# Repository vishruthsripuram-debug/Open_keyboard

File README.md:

# Nano pad
A 4 key macro pad that you can program actions to.

## Design
My inspiration for this macro pad was the printed pad by prota design but i wanted to make something smaller and cheaper than both of their offering the printed pad and glyff. The printed pad being $68 seemed quite unreasonable to me seeing as it was only a screen a few key swicthes and a microcontroller.

I wanted the project to be simple and easily accessible and customisable by many people so all of the PCB design files are included in the rep for download and printing from a pcb service. The case is 3d printable in any colour you like and customisable to include a knob or other features as step and other cad files are included. The model has also been published on makerworld for the ease of use with Bambulab printers. The whole idea is to hace a simple good looking macro pad that anyone can own for under $15 USD, for 25 USD you can own 5 macro pads.

## BOM

## Bill of Materials — Macro Pad

| Item # | Designator | Qty | Manufacturer | Mfg Part # | Description / Value | Package/Footprint | Type | Notes |
|---|---|---|---|---|---|---|---|---|
| 1 | SW1, SW2, SW3, SW4 | 4 | Cherry (preferred) | MX1A-G1NW | MX Brown, tactile, PCB mount, 5-pin | SW_Cherry_MX_1.00u_PCB | THT | If out of stock, substitute OK: any 5-pin PCB-mount MX-compatible Brown tactile switch (e.g. Gateron KS-3 Brown, Kailh Box/MX Brown, Outemu Brown) — all fit this footprint |
| 2 | U1 | 1 | DFRobot | DFR0648 | Fermion 0.91" 128x32 SSD1306 OLED, I2C, top-mounted pin header (OLED-B) | Module, pin header, THT | THT | Pins are on the short top edge, NOT the long side — confirm this exact pinout before substituting |
| 3 | U2 | 1 | Seeed Studio | 101991470 | XIAO ESP32-C6 module (Tape and Reel, SMD variant) | SMD castellated module | SMD | — |

## Software

## Collaboration
In collaboration with PCBWay

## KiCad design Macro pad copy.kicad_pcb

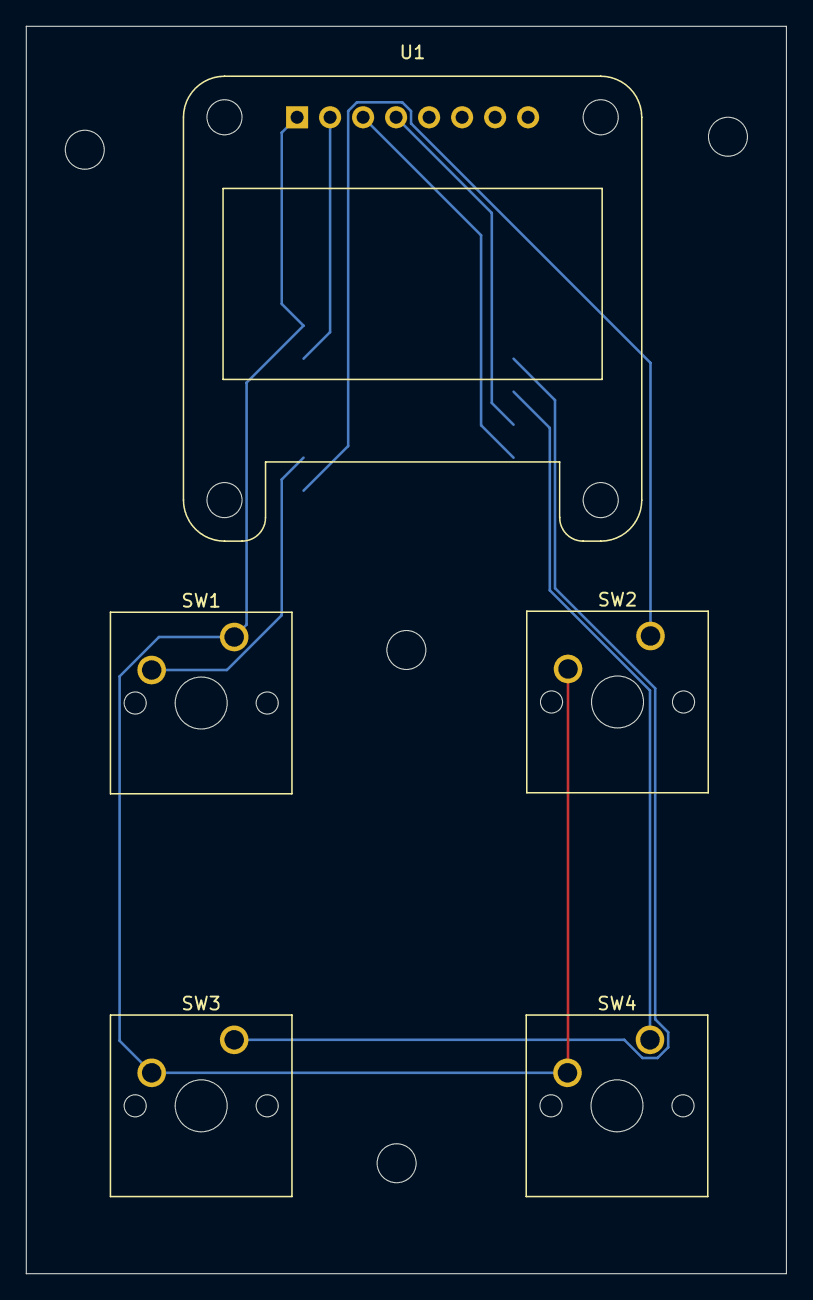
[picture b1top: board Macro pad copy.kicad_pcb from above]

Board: 2 copper layers, 58.5 x 96.0 mm, 6 parts (1 on the bottom side), 8 nets.

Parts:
SW1, SW2, SW3, SW4: SW_Push; SW_Cherry_MX_1.00u_PCB
U1: ER_OLEDM0.91_1x-I2C; Adafruit_SSD1306
U2: MOUDLE-SEEEDUINO-XIAO; XIAO-ESP32-C6-SMD

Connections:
GND: SW1.1, SW2.2, SW3.2, SW4.2, U1.1 (GND), U2.13 (GND)
unnamed: U1.3 (SCL), U2.6 (PA9_A5_D5_SCL)
unnamed: U1.4 (SDA), U2.5 (PA8_A4_D4_SDA)
unnamed: U1.2 (VCC), U2.12 (3V3)
unnamed: SW1.2, U2.9 (PA7_A8_D8_SCK)
unnamed: SW3.1, U2.3 (PA10_A2_D2)
unnamed: SW4.1, U2.4 (PA11_A3_D3)
unnamed: SW2.1, U2.8 (PB09_A7_D7_RX)

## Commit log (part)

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2026-05-01 PCB files upload
2026-05-23 adding journal
2026-05-23 Update Journal with macropad project details
    Documented progress on custom macropad project, including coding, design, and PCB development.
2026-05-23 Rename Journal to journal.md
2026-05-23 Rename journal.md to JOURNAL.md
